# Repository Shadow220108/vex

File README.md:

<h1 align="center">
<br>

<br>
Vex
<br>
</h1>

<h3 align="center">

A round 7 port USB hub :D

</h3>

<div align="center">

</div>

Vex is a USB 2.0 hub built around the FE2.1 chip. You plug it into your laptop with one USB-C cable and it gives you 7 ports around the edge, 3 USB-C and 4 USB-A. The board is a 70 mm circle with 4 layers, cause I didn't want another boring rectangle hub.

The whole design process is in [JOURNAL.md](JOURNAL.md), it took me around 39 hours.

## Features

- FE2.1 USB 2.0 hub chip with 7 downstream ports
- 1 USB-C upstream port, 3 USB-C and 4 USB-A downstream ports
- Ports split into 2 power groups, each with its own polyfuse (2A and 1.5A) and an AO3401A power switch controlled by the hub
- Overcurrent sensing, so the hub knows if a port shorts
- SMAJ5.0A TVS diode and reverse current protection on the input
- 47uF cap on every downstream port so plugging something in doesn't dip the others
- 56k CC pullups on the USB-C downstream ports so phones and other USB-C devices get power
- Blue power LED and red hub active LED
- Bus powered, all ports share what the laptop port gives

## Ports

| Port | Type | Power group |
| --- | --- | --- |
| Upstream | USB-C | Input from laptop |
| 1 to 4 | Downstream | Group A, 2A fuse |
| 5 to 7 | Downstream | Group B, 1.5A fuse |

## Schematic

| Full schematic |
| --- |
|  |

| Upstream port | Hub chip |
| --- | --- |
|  |  |

## PCB

| Routed | Ground pour |
| --- | --- |
|  |  |

The FE2.1 sits in the middle so the USB lines to every port are about the same length. Top and bottom have ground fills, inner 1 is a ground plane and inner 2 is a 3.3V plane. The power traces are 0.8 mm and there are 107 vias stitching it all together.

## Firmware 

Since the USB HUB uses, plug and play IC, this project requires no firmware

| Back |
| --- |
|  |

## Why was it made?

My laptop only has 2 USB ports and I'm always running out. So I made my own hub, and made it round so it actually looks cool on my desk :D

## BOM

| Item | Qty | Price ($) | Vendor |
| --- | --- | --- | --- |
| PCBA (2 boards) | 1 | 35.70 | JLCPCB |
| Total | | 35.70 | |

## Here is the full bom of LCSC parts from KiCAD 

|Designator         |Footprint                                              |Quantity|Value                      |LCSC Part #|Part Name                                    |Unit Price (USD)|Ext Price (USD)|Price Tier|
|-------------------|-------------------------------------------------------|--------|---------------------------|-----------|---------------------------------------------|----------------|---------------|----------|
|C1, C15, C16       |1210                                                   |3       |100uF                      |C49066     |Samsung CL32A107MQVNNNE (6.3V)               |0.1241          |0.3723         |2+        |
|C10, C11, C14, C4, C6, C7, C8|0603                                                   |7       |100nF                      |C14663     |Yageo CC0603KRX7R9BB104                      |0.0025          |0.0175         |1+        |
|C12, C13           |0603                                                   |2       |18pF                       |C1647      |Samsung CL10C180JB8NNNC                      |0.0159          |0.0318         |100+      |
|C17, C18, C19, C20, C21, C22, C23|1206                                                   |7       |47uF                       |C96123     |Samsung CL31A476MPHNNNE (10V)                |0.0705          |0.4935         |10+       |
|C2, C3, C5, C9     |0805                                                   |4       |10uF                       |C15850     |Samsung CL21A106KAYNNNE                      |0.0856          |0.3424         |20+       |
|D1                 |D_SMA                                                  |1       |SMAJ5.0A                   |C113952    |MDD SMAJ5.0A                                 |0.0344          |0.0344         |20+       |
|D2                 |0603                                                   |1       |Power-Blue                 |C72041     |Everlight 19-217/BHC-ZL1M2RY/3T              |0.0172          |0.0172         |20+       |
|D3                 |0603                                                   |1       |Hub-Active Red             |C2286      |Hubei KENTO KT-0603R                         |0.0065          |0.0065         |100+      |
|F1                 |1812                                                   |1       |2A hold (1812)             |C49073033  |BORN SMD1812-200/16N (PTC 16V)               |0.0272          |0.0272         |10+       |
|F2                 |1812                                                   |1       |1.5A hold (1812)           |C46641160  |R+O SMD1812-150-16 (PTC 16V)                 |0.0634          |0.0634         |10+       |
|J1, J2, J3, J4     |USB_C_Receptacle_HRO_TYPE-C-31-M-12                    |4       |USB_C_Receptacle_USB2.0_16P|C165948    |Korean Hroparts TYPE-C-31-M-12               |0.1750          |0.7000         |5+        |
|J5, J6, J7, J8     |USB_A_Molex_67643_Horizontal                           |4       |USB_A                      |C564920    |Molex 676432910                              |0.9326          |3.7304         |1+        |
|Q1, Q2, Q3         |SOT-23                                                 |3       |AO3401A                    |C15127     |AOS AO3401A                                  |0.0629          |0.1887         |10+       |
|R1, R2             |0603                                                   |2       |5.1K                       |C23186     |UNI-ROYAL 0603WAF5101T5E                     |0.0012          |0.0024         |100+      |
|R10, R11, R12, R13, R14, R15|0603                                                   |6       |56K                        |C23206     |UNI-ROYAL 0603WAF5602T5E                     |0.0020          |0.0120         |100+      |
|R3, R8             |0603                                                   |2       |1K                         |C21190     |UNI-ROYAL 0603WAF1001T5E                     |0.0010          |0.0020         |100+      |
|R4, R5             |0603                                                   |2       |100K                       |C25803     |UNI-ROYAL 0603WAF1003T5E                     |0.0015          |0.0030         |100+      |
|R6                 |0603                                                   |1       |2.7K 1%                    |C13167     |UNI-ROYAL 0603WAF2701T5E                     |0.0010          |0.0010         |100+      |
|R7, R9             |0603                                                   |2       |10K                        |C25804     |UNI-ROYAL 0603WAF1002T5E                     |0.0010          |0.0020         |100+      |
|U1                 |LQFP-48_L7.0-W7.0-P0.50-LS9.0-BL                       |1       |FE2.1                      |C39693     |Terminus FE2.1-CQFP48A                       |1.7038          |1.7038         |1+        |
|Y1                 |Crystal_SMD_3225-4Pin_3.2x2.5mm                        |1       |12MHz                      |C70565     |YXC X322512MOB4SI (12pF load)                |0.0974          |0.0974         |5+        |

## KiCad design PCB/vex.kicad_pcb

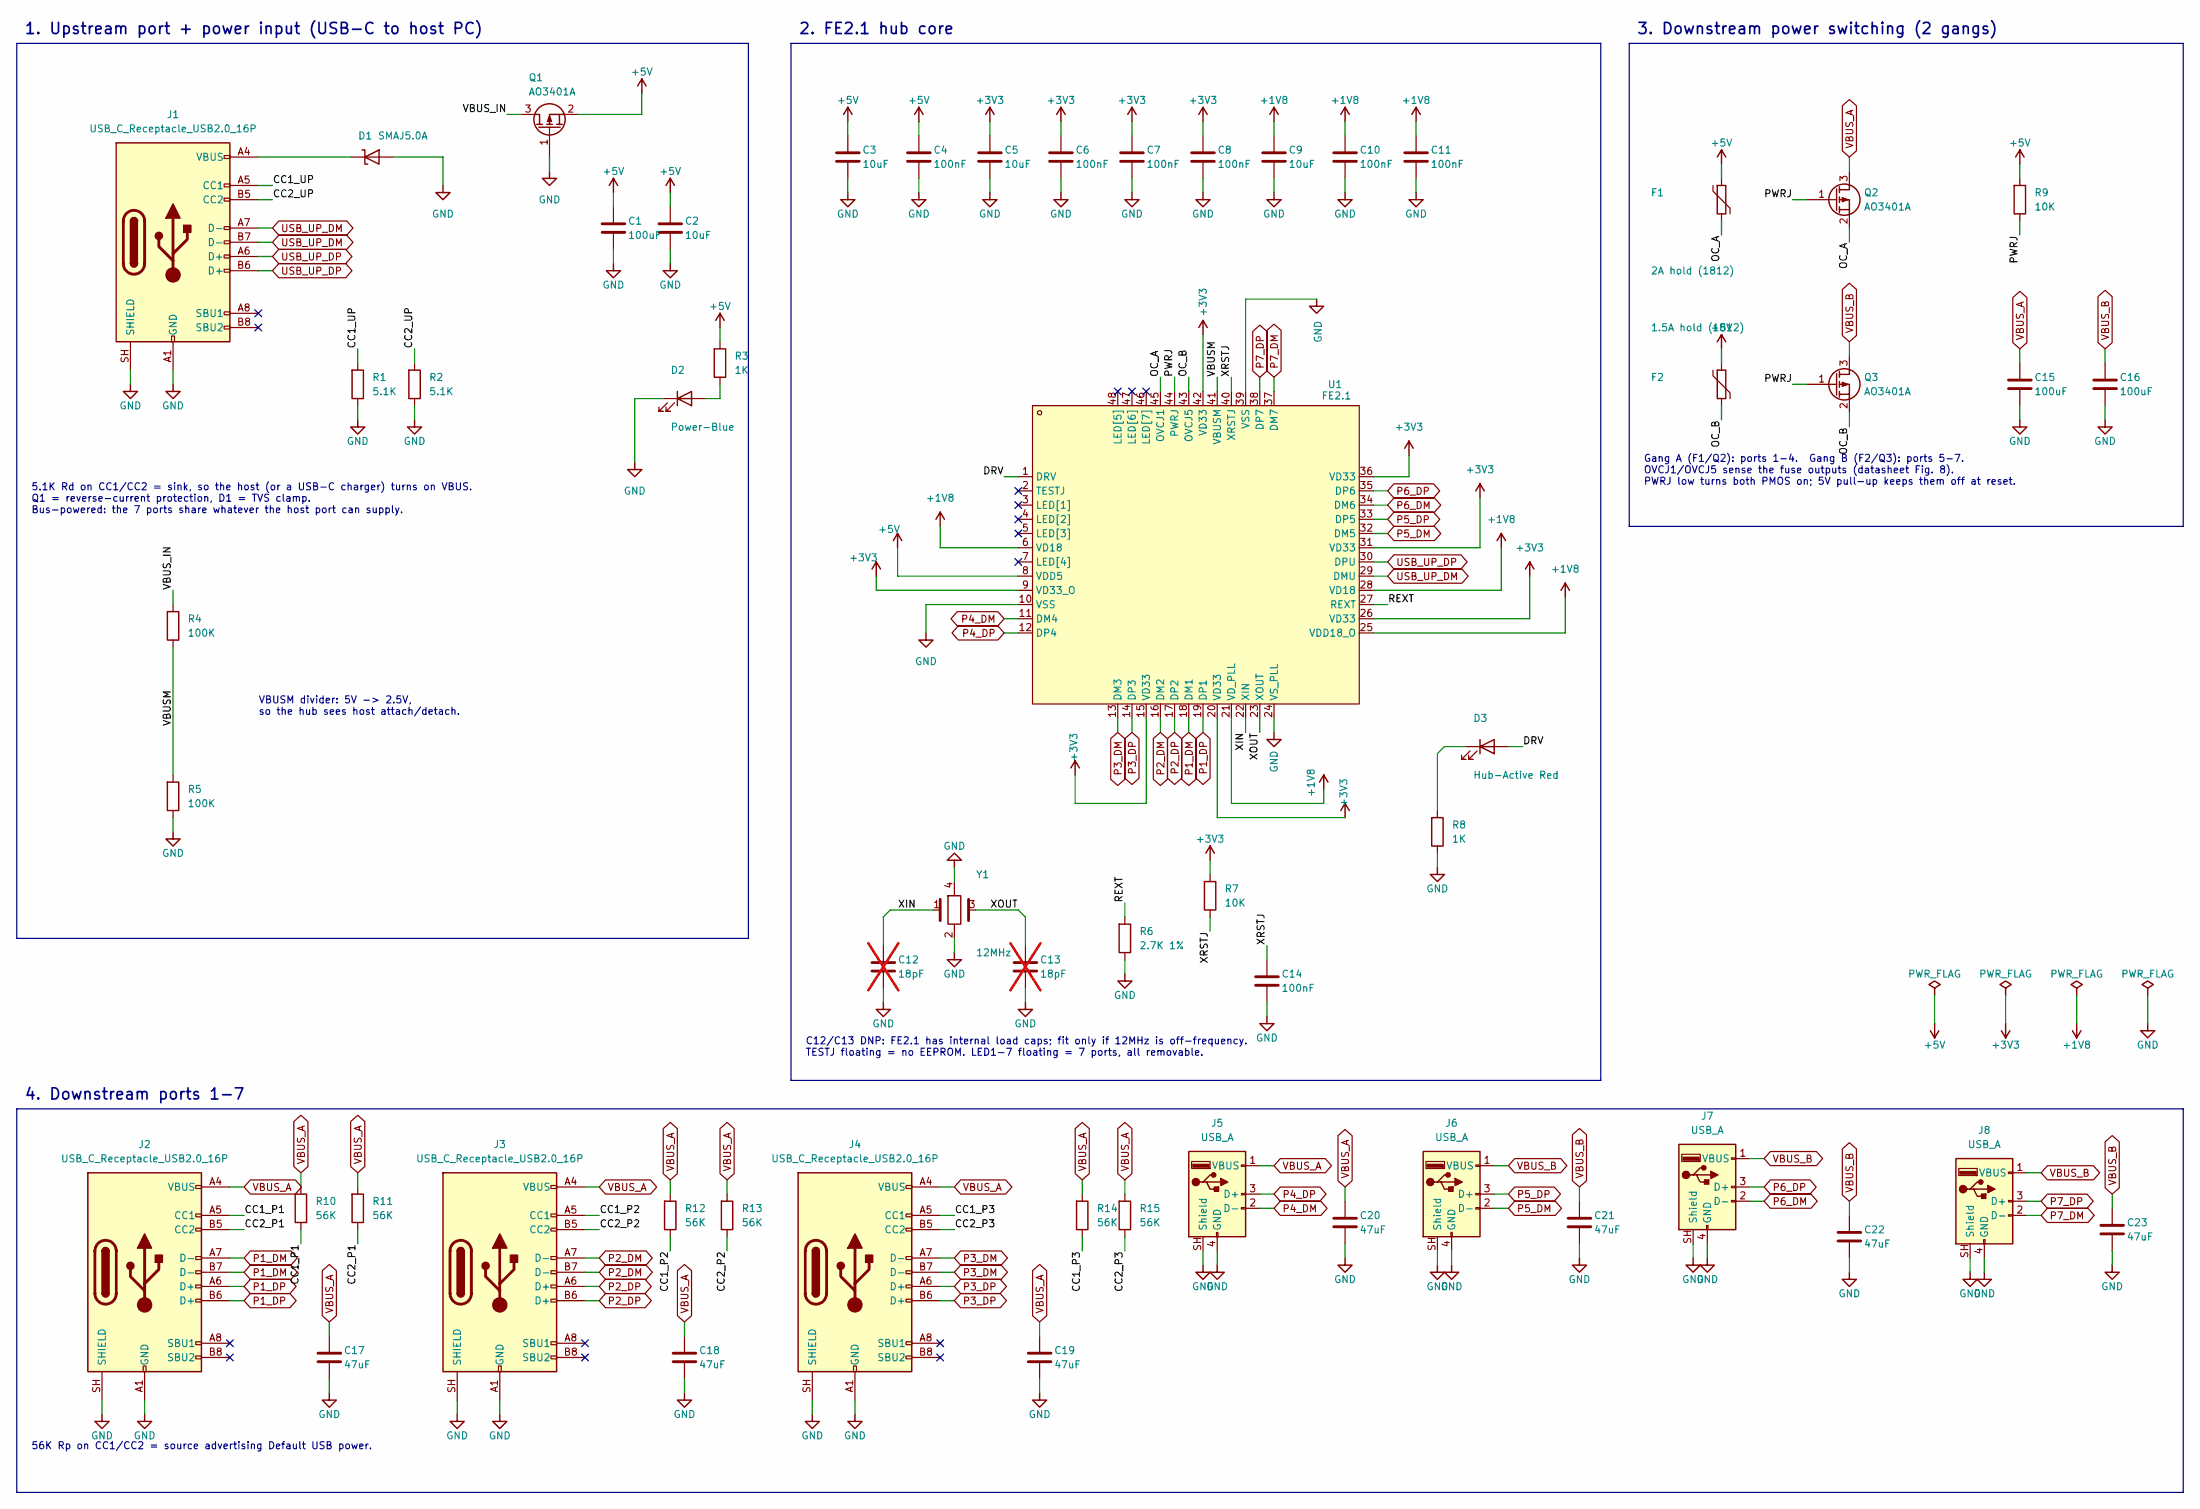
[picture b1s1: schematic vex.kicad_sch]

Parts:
C1, C15, C16: 100uF; C_1210_3225Metric
C2, C3, C5, C9: 10uF; C_0805_2012Metric
C4, C6, C7, C8, C10, C11, C14: 100nF; C_0603_1608Metric
C12, C13: 18pF; C_0603_1608Metric; not fitted
C17, C18, C19, C20, C21, C22, C23: 47uF; C_1206_3216Metric
D1: SMAJ5.0A; D_SMA
D2: Power-Blue; LED_0603_1608Metric
D3: Hub-Active Red; LED_0603_1608Metric
F1: 2A hold (1812); Fuse_1812_4532Metric
F2: 1.5A hold (1812); Fuse_1812_4532Metric
J1, J2, J3, J4: USB_C_Receptacle_USB2.0_16P; USB_C_Receptacle_HRO_TYPE-C-31-M-12
J5, J6, J7, J8: USB_A; USB_A_Molex_67643_Horizontal
Q1, Q2, Q3: AO3401A; SOT-23
R1, R2: 5.1K; R_0603_1608Metric
R3, R8: 1K; R_0603_1608Metric
R4, R5: 100K; R_0603_1608Metric
R6: 2.7K 1%; R_0603_1608Metric
R7, R9: 10K; R_0603_1608Metric
R10, R11, R12, R13, R14, R15: 56K; R_0603_1608Metric
U1: FE2.1; LQFP-48_L7.0-W7.0-P0.50-LS9.0-BL; MPN FE2.1-CQFP48A; LCSC Part C39693
Y1: 12MHz; Crystal_SMD_3225-4Pin_3.2x2.5mm

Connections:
+1V8: C9.1, C10.1, C11.1, U1.6 (VD18), U1.21 (VD_PLL), U1.25 (VDD18_O), U1.28 (VD18)
+3V3: C5.1, C6.1, C7.1, C8.1, R7.1, U1.9 (VD33_O), U1.15 (VD33), U1.20 (VD33), U1.26 (VD33), U1.31 (VD33), U1.36 (VD33), U1.42 (VD33)
+5V: C1.1, C2.1, C3.1, C4.1, F1.1, F2.1, Q1.2 (S), R3.1, R9.1, U1.8 (VDD5)
/CC1_P1: J2.A5 (CC1), R10.2
/CC1_P2: J3.A5 (CC1), R12.2
/CC1_P3: J4.A5 (CC1), R14.2
/CC1_UP: J1.A5 (CC1), R1.1
/CC2_P1: J2.B5 (CC2), R11.2
/CC2_P2: J3.B5 (CC2), R13.2
/CC2_P3: J4.B5 (CC2), R15.2
/CC2_UP: J1.B5 (CC2), R2.1
/DRV: D3.2 (A), U1.1 (DRV)
/OC_A: F1.2, Q2.2 (S), U1.45 (OVCJ1)
/OC_B: F2.2, Q3.2 (S), U1.43 (OVCJ5)
/PWRJ: Q2.1 (G), Q3.1 (G), R9.2, U1.44 (PWRJ)
/REXT: R6.1, U1.27 (REXT)
/VBUSM: R4.2, R5.1, U1.41 (VBUSM)
/VBUS_IN: Q1.3 (D), R4.1
/XIN: C12.1, U1.22 (XIN), Y1.1
/XOUT: C13.1, U1.23 (XOUT), Y1.3
/XRSTJ: C14.1, R7.2, U1.40 (XRSTJ)
GND: C1.2, C2.2, C3.2, C4.2, C5.2, C6.2, C7.2, C8.2, C9.2, C10.2, C11.2, C12.2, C13.2, C14.2, C15.2, C16.2, C17.2, C18.2, C19.2, C20.2, C21.2, C22.2, C23.2, D1.2 (A), D2.1 (K), J1.A1 (GND), J1.A12 (GND), J1.B1 (GND), J1.B12 (GND), J1.SH (SHIELD), J2.A1 (GND), J2.A12 (GND), J2.B1 (GND), J2.B12 (GND), J2.SH (SHIELD), J3.A1 (GND), J3.A12 (GND), J3.B1 (GND), J3.B12 (GND), J3.SH (SHIELD), J4.A1 (GND), J4.A12 (GND), J4.B1 (GND), J4.B12 (GND), J4.SH (SHIELD), J5.4 (GND), J5.SH (Shield), J6.4 (GND), J6.SH (Shield), J7.4 (GND), J7.SH (Shield), J8.4 (GND), J8.SH (Shield), Q1.1 (G), R1.2, R2.2, R5.2, R6.2, R8.2, U1.10 (VSS), U1.24 (VS_PLL), U1.39 (VSS), Y1.2, Y1.4
unnamed: D1.1 (K), J1.A4 (VBUS), J1.A9 (VBUS), J1.B4 (VBUS), J1.B9 (VBUS)
unnamed: D2.2 (A), R3.2
unnamed: D3.1 (K), R8.1
P1_DM: J2.A7 (D-), J2.B7 (D-), U1.18 (DM1)
P1_DP: J2.A6 (D+), J2.B6 (D+), U1.19 (DP1)
P2_DM: J3.A7 (D-), J3.B7 (D-), U1.16 (DM2)
P2_DP: J3.A6 (D+), J3.B6 (D+), U1.17 (DP2)
P3_DM: J4.A7 (D-), J4.B7 (D-), U1.13 (DM3)
P3_DP: J4.A6 (D+), J4.B6 (D+), U1.14 (DP3)
P4_DM: J5.2 (D-), U1.11 (DM4)
P4_DP: J5.3 (D+), U1.12 (DP4)
P5_DM: J6.2 (D-), U1.32 (DM5)
P5_DP: J6.3 (D+), U1.33 (DP5)
P6_DM: J7.2 (D-), U1.34 (DM6)
P6_DP: J7.3 (D+), U1.35 (DP6)
P7_DM: J8.2 (D-), U1.37 (DM7)
P7_DP: J8.3 (D+), U1.38 (DP7)
USB_UP_DM: J1.A7 (D-), J1.B7 (D-), U1.29 (DMU)
USB_UP_DP: J1.A6 (D+), J1.B6 (D+), U1.30 (DPU)
VBUS_A: C15.1, C17.1, C18.1, C19.1, C20.1, J2.A4 (VBUS), J2.A9 (VBUS), J2.B4 (VBUS), J2.B9 (VBUS), J3.A4 (VBUS), J3.A9 (VBUS), J3.B4 (VBUS), J3.B9 (VBUS), J4.A4 (VBUS), J4.A9 (VBUS), J4.B4 (VBUS), J4.B9 (VBUS), J5.1 (VBUS), Q2.3 (D), R10.1, R11.1, R12.1, R13.1, R14.1, R15.1
VBUS_B: C16.1, C21.1, C22.1, C23.1, J6.1 (VBUS), J7.1 (VBUS), J8.1 (VBUS), Q3.3 (D)

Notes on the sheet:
4. Downstream ports 1-7
C12/C13 DNP: FE2.1 has internal load caps; fit only if 12MHz is off-frequency. TESTJ floating = no EEPROM. LED1-7 floating = 7 ports, all removable.
VBUSM divider: 5V -> 2.5V, so the hub sees host attach/detach.
Gang A (F1/Q2): ports 1-4. Gang B (F2/Q3): ports 5-7. OVCJ1/OVCJ5 sense the fuse outputs (datasheet Fig. 8). PWRJ low turns both PMOS on; 5V pull-up keeps them off at reset.
1. Upstream port + power input (USB-C to host PC)
56K Rp on CC1/CC2 = source advertising Default USB power.
2. FE2.1 hub core
3. Downstream power switching (2 gangs)
5.1K Rd on CC1/CC2 = sink, so the host (or a USB-C charger) turns on VBUS. Q1 = reverse-current protection, D1 = TVS clamp. Bus-powered: the 7 ports share whatever the host port can supply.

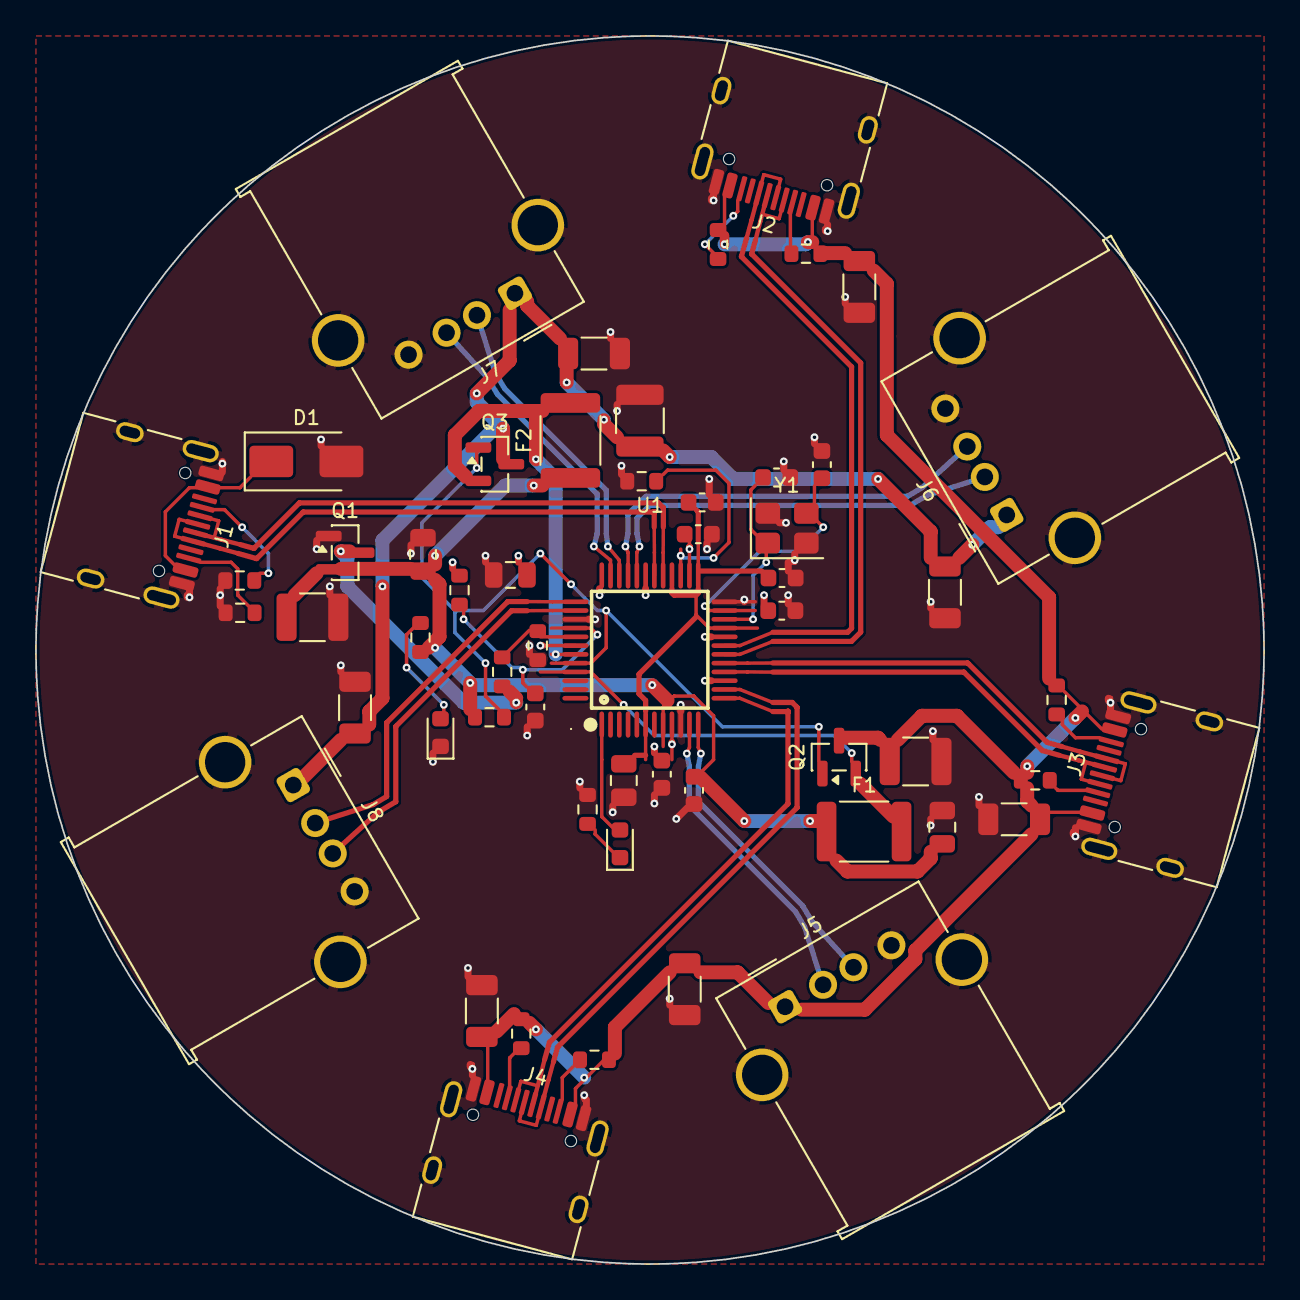
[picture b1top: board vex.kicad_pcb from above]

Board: 4 copper layers, 70.0 x 70.0 mm, 56 parts (0 on the bottom side), 43 nets.

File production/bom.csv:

Designator,Footprint,Quantity,Value,LCSC Part #
"C1, C15, C16",1210,3,100uF,
"C10, C11, C14, C4, C6, C7, C8",0603,7,100nF,
"C12, C13",0603,2,18pF,
"C17, C18, C19, C20, C21, C22, C23",1206,7,47uF,
"C2, C3, C5, C9",0805,4,10uF,
D1,D_SMA,1,SMAJ5.0A,
D2,0603,1,Power-Blue,
D3,0603,1,Hub-Active Red,
F1,1812,1,2A hold (1812),
F2,1812,1,1.5A hold (1812),
"J1, J2, J3, J4",USB_C_Receptacle_HRO_TYPE-C-31-M-12,4,USB_C_Receptacle_USB2.0_16P,
"J5, J6, J7, J8",USB_A_Molex_67643_Horizontal,4,USB_A,
"Q1, Q2, Q3",SOT-23,3,AO3401A,
"R1, R2",0603,2,5.1K,
"R10, R11, R12, R13, R14, R15",0603,6,56K,
"R3, R8",0603,2,1K,
"R4, R5",0603,2,100K,
R6,0603,1,2.7K 1%,
"R7, R9",0603,2,10K,
U1,LQFP-48_L7.0-W7.0-P0.50-LS9.0-BL,1,FE2.1,C39693
Y1,Crystal_SMD_3225-4Pin_3.2x2.5mm,1,12MHz,
